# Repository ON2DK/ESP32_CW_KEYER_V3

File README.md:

# ESP32_CW_KEYER_V3
ESP32_CW_KEYER_V3

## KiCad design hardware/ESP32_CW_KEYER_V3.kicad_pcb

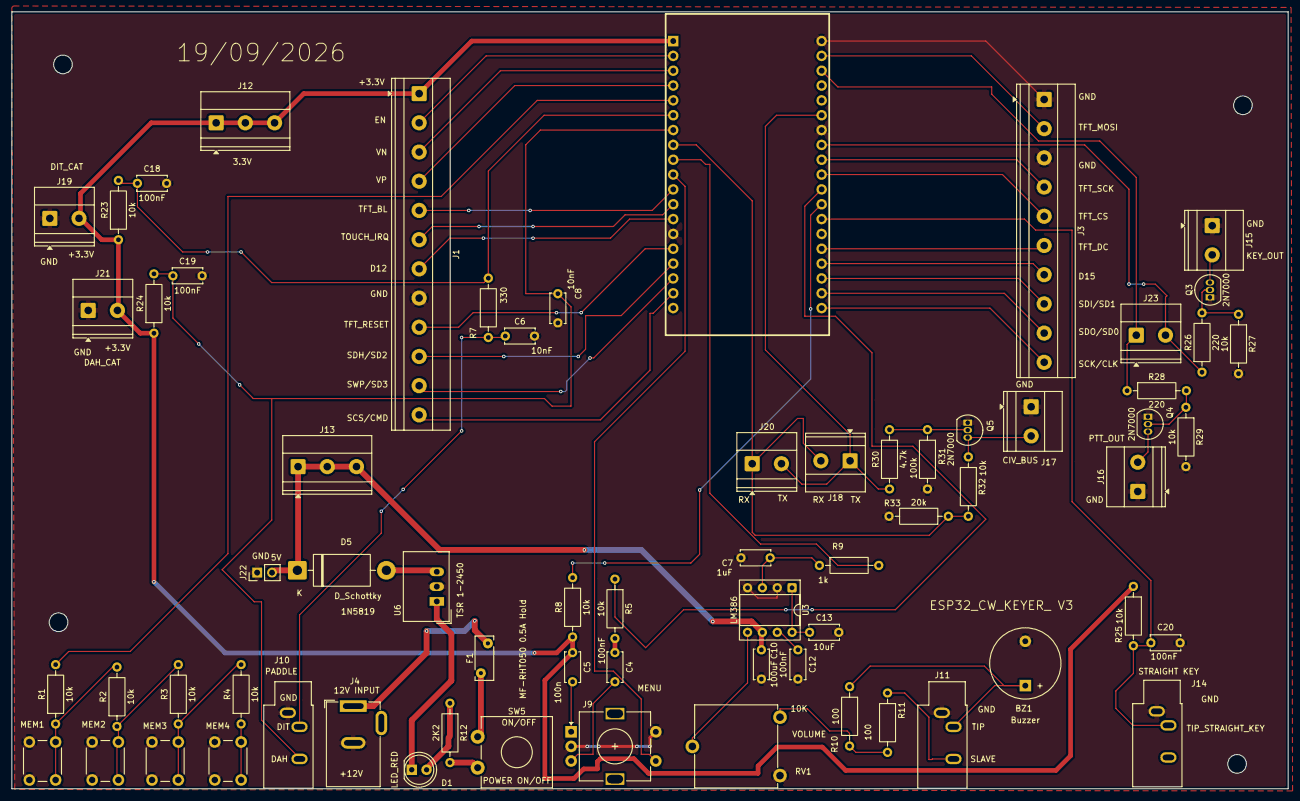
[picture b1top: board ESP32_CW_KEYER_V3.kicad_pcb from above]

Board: 2 copper layers, 218.5 x 133.0 mm, 67 parts (0 on the bottom side), 60 nets.

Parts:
BZ1: Buzzer; Buzzer_12x9.5RM7.6
C4, C12, C18, C19, C20: 100nF; C_Disc_D5.0mm_W2.5mm_P5.00mm
C5: 100n; C_Disc_D5.0mm_W2.5mm_P5.00mm
C6, C8: 10nF; C_Disc_D5.0mm_W2.5mm_P5.00mm
C7: 1uF; C_Disc_D5.0mm_W2.5mm_P5.00mm
C10: 100uF; C_Disc_D5.0mm_W2.5mm_P5.00mm
C13: 10uF; C_Disc_D5.0mm_W2.5mm_P5.00mm
D1: LED_RED; LED_D5.0mm
D5: D_Schottky; D_DO-201AD_P15.24mm_Horizontal
F1: MF-RHT050 0.5A Hold; Fuse_Bourns_MF-RHT050
J1: Conn_01x12; TerminalBlock_Phoenix_MKDS-1,5-12_1x12_P5.00mm_Horizontal
J3: Conn_01x10; TerminalBlock_Phoenix_MKDS-1,5-10_1x10_P5.00mm_Horizontal
J4: Barrel_Jack_Switch; BarrelJack_GCT_DCJ200-10-A_Horizontal
J9: RotaryEncoder_Switch; RotaryEncoder_Alps_EC11E-Switch_Vertical_H20mm
J10, J11, J14: AudioJack3; Jack_3.5mm_CUI_SJ1-3533NG_Horizontal
J12, J13: Conn_01x03; TerminalBlock_Phoenix_MKDS-1,5-3_1x03_P5.00mm_Horizontal
J15, J16, J17, J18, J19, J20, J21, J23: Conn_01x02; TerminalBlock_Phoenix_MKDS-1,5-2_1x02_P5.00mm_Horizontal
J22: Conn_01x02; PinHeader_1x02_P2.54mm_Vertical
MEM1, MEM2, MEM3, MEM4: SW_Push; SW_PUSH_6mm_H13mm
Q3, Q4, Q5: 2N7000; TO-92_Inline
R1, R2, R3, R4, R5, R8, R23, R24, R25, R27, R29, R32: 10k; R_Axial_DIN0207_L6.3mm_D2.5mm_P10.16mm_Horizontal
R7: 330; R_Axial_DIN0207_L6.3mm_D2.5mm_P10.16mm_Horizontal
R9: 1k; R_Axial_DIN0207_L6.3mm_D2.5mm_P10.16mm_Horizontal
R10, R11: 100; R_Axial_DIN0207_L6.3mm_D2.5mm_P10.16mm_Horizontal
R12: 2K2; R_Axial_DIN0207_L6.3mm_D2.5mm_P10.16mm_Horizontal
R26, R28: 220; R_Axial_DIN0207_L6.3mm_D2.5mm_P10.16mm_Horizontal
R30: 4.7k; R_Axial_DIN0207_L6.3mm_D2.5mm_P10.16mm_Horizontal
R31: 100k; R_Axial_DIN0207_L6.3mm_D2.5mm_P10.16mm_Horizontal
R33: 20k; R_Axial_DIN0207_L6.3mm_D2.5mm_P10.16mm_Horizontal
RV1: 10K; Potentiometer_ACP_CA14V-15_Vertical
SW5: POWER ON/OFF; SW_CW_GPTS203211B
U2: ESP32-WROOM-32; ESP32_DevKit_38P
U3: LM386; DIP-8_W7.62mm_Socket
U6: TSR 1-2450; Converter_DCDC_TRACO_TSR-1_THT

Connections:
+3.3V: C5.1, J1.1, J12.1, J12.2, J12.3, J19.2, J21.2, R8.1, R23.1, R24.1, R25.1, U2.2 (VDD)
+5V: C10.1, D5.1 (K), J13.1, J13.2, J13.3, J22.2, U3.6 (V+)
/AUDIO: R9.2, U2.10 (IO25)
/BUTTON_ADC: R1.2, U2.6 (IO34)
/CAT_RX: J18.2, J20.1, R32.2, R33.1, U2.9 (IO33)
/CAT_TX: J18.1, J20.2, R30.1, U2.33 (IO21)
/CIV_BUS: J17.2, Q5.3 (D), R32.1
/D12: J1.7, U2.14 (IO12)
/D15: J3.7, U2.23 (IO15)
/DAH: C8.1, C19.1, J10.R, R24.2, U2.8 (IO32)
/DIT: C18.1, R7.2, R23.2, U2.7 (IO35)
/EN: J1.2, U2.3 (EN)
/ENC_A: R8.2, U2.27 (IO16)
/ENC_B: R5.1, U2.28 (IO17)
/ENC_SW: J9.S1, U2.11 (IO26)
/KEY_CTRL: J23.2, R26.1, U2.31 (IO19)
/KEY_OUT: J15.2, Q3.3 (D)
/PTT_CTRL: J23.1, R28.1, U2.36 (IO22)
/PTT_OUT: J16.2, Q4.3 (D)
/SCK/CLK: J3.10, U2.20 (SCK/CLK)
/SCS/CMD: J1.12, U2.19 (SCS/CMD)
/SDI/SD1: J3.8, U2.22 (SDI/SD1)
/SDO/SD0: J3.9, U2.21 (SDO/SD0)
/SHD/SD2: J1.10, U2.17 (SHD/SD2)
/STRAIGHT_KEY: C20.1, J14.T, R25.2, U2.26 (IO4)
/SWP/SD3: J1.11, U2.18 (SWP/SD3)
/TFT_BL: J1.5, U2.12 (IO27)
/TFT_CS: J3.5, U2.29 (IO5)
/TFT_DC: J3.6, U2.24 (IO2)
/TFT_MOSI: J3.2, U2.37 (IO23)
/TFT_RESET: J1.9, U2.16 (IO13)
/TFT_SCK: J3.4, U2.30 (IO18)
/TOUCH_IRQ: J1.6, U2.13 (IO14)
/VN: J1.3, U2.4 (SENSOR_VP)
/VP: J1.4, U2.5 (SENSOR_VN)
GND: BZ1.2 (-), C6.2, C7.1, C8.2, C10.2, C12.2, C13.2, C18.2, C19.2, C20.2, J1.8, J3.1, J3.3, J4.2, J9.C, J9.S2, J10.S, J11.S, J14.S, J15.1, J16.1, J17.1, J19.1, J21.1, J22.1, MEM1.1, MEM2.1, MEM3.1, MEM4.1, Q3.1 (S), Q4.1 (S), Q5.1 (S), R27.2, R29.2, R31.2, R33.2, RV1.3, U2.1 (GND), U2.15 (GND), U2.38 (GND), U3.2 (-), U3.4 (GND), U6.2 (GND)
unnamed: BZ1.1 (+), J11.T, R10.1
unnamed: C4.1, R5.2
unnamed: C4.2, J9.B
unnamed: C5.2, J9.A
unnamed: C6.1, J10.T, R7.1
unnamed: C13.1, U3.1 (GAIN), U3.8 (GAIN)
unnamed: D1.2 (A), R12.1
unnamed: D1.1 (K), U6.1 (IN)
unnamed: D5.2 (A), U6.3 (OUT)
unnamed: F1.2, J4.1
unnamed: J11.R, R11.1
unnamed: MEM1.2, R1.1, R2.2
unnamed: MEM2.2, R2.1, R3.2
unnamed: MEM3.2, R3.1, R4.2
unnamed: MEM4.2, R4.1
unnamed: Q3.2 (G), R26.2, R27.1
unnamed: Q4.2 (G), R28.2, R29.1
unnamed: Q5.2 (G), R30.2, R31.1
unnamed: R10.2, R11.2, RV1.1
unnamed: RV1.2, U3.5
unnamed: F1.1, SW5.1 (A)
unnamed: R12.2, SW5.2 (B)
unnamed: C7.2, R9.1, U3.3 (+)
unnamed: C12.1, U3.7 (BYPASS)
